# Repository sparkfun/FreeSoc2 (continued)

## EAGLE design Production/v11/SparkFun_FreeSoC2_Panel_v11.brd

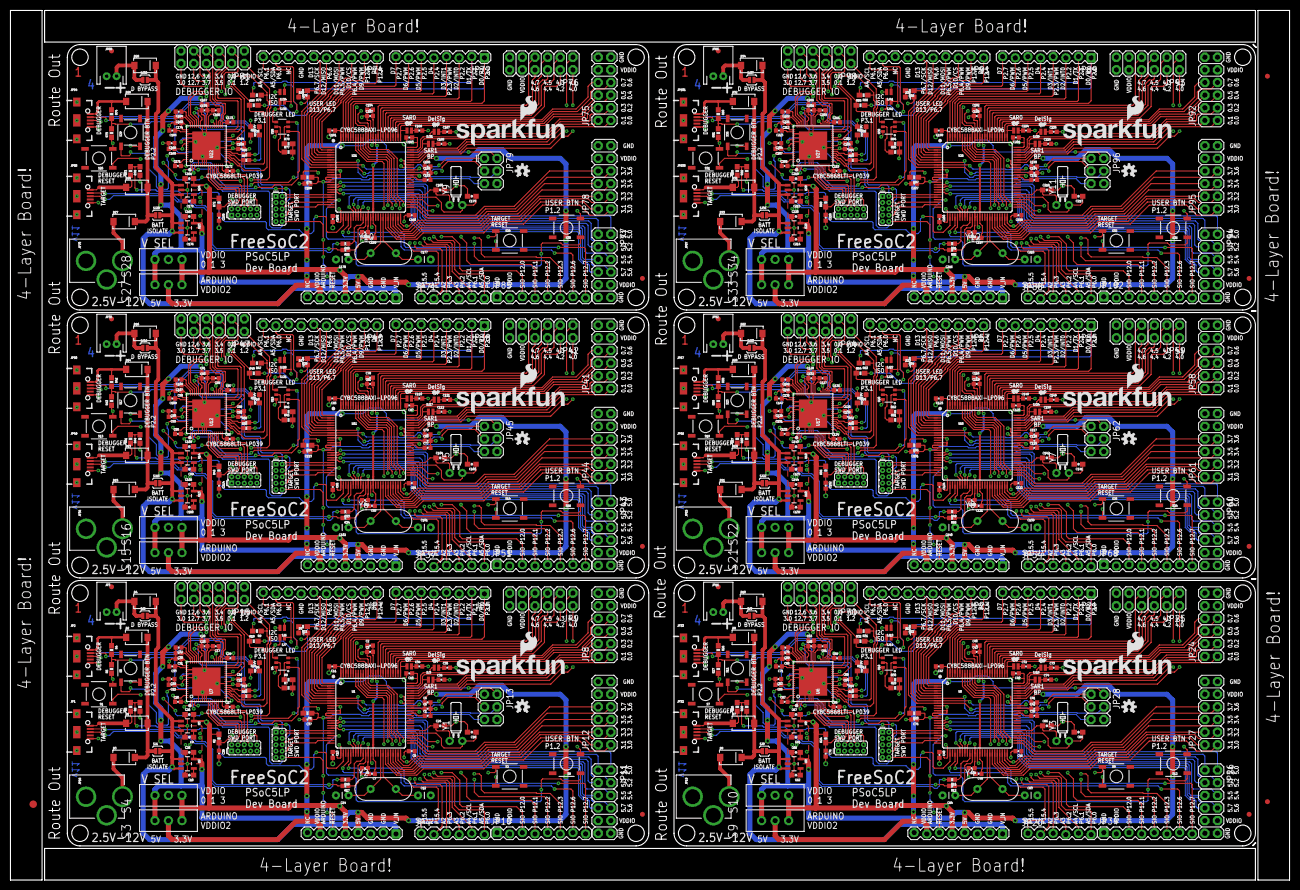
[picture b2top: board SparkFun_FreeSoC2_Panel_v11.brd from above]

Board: 4 copper layers, 257.0 x 174.8 mm, 633 parts (0 on the bottom side), 756 nets.

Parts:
C1, C2, C4, C5, C7, C16, C17, C19, C20, C39, C40, C41, C44, C45, C50, C51, C52, C53, C77, C78, C79, C82, C83, C88, C89, C90, C91, C115, C116, C117, C120, C121, C126, C127, C128, C129, C153, C154, C155, C158, C159, C164, C165, C166, C167, C191, C192, C193, C196, C197, C202, C203, C204, C205: 1.0uF; 0402-CAP
C3, C6, C9, C11, C13, C15, C21, C22, C23, C25, C27, C29, C30, C31, C32, C33, C34, C35, C36, C37, C38, C42, C43, C46, C47, C48, C49, C54, C55, C56, C57, C58, C59, C60, C69, C70, C71, C72, C73, C74, C75, C76, C80, C81, C84, C85, C86, C87, C92, C93, C94, C95, C96, C97, C98, C107, C108, C109, C110, C111, C112, C113, C114, C118, C119, C122, C123, C124, C125, C130, C131, C132, C133, C134, C135, C136, C145, C146, C147, C148, C149, C150, C151, C152, C156, C157, C160, C161, C162, C163, C168, C169, C170, C171, C172, C173, C174, C183, C184, C185, C186, C187, C188, C189, C190, C194, C195, C198, C199, C200, C201, C206, C207, C208, C209, C210, C211, C212, C221, C222, C223, C224, C225, C226, C227, C228: 0.1uF; 0402-CAP
C8, C10, C61, C62, C99, C100, C137, C138, C175, C176, C213, C214: 470pF; 0603-CAP
C12, C14, C63, C64, C101, C102, C139, C140, C177, C178, C215, C216: CAP-PTH-SMALL
C18, C24, C65, C66, C103, C104, C141, C142, C179, C180, C217, C218: 22pF; 0603-CAP
C26, C28, C67, C68, C105, C106, C143, C144, C181, C182, C219, C220: 2.2uF; 0603-CAP
D1, D2, D3, D4, D7, D8, D9, D10, D13, D14, D15, D16, D19, D20, D21, D22, D25, D26, D27, D28, D31, D32, D33, D34: MBRA140; SMA-DIODE
D5, D6, D11, D12, D17, D18, D23, D24, D29, D30, D35, D36: RED; LED-0603
E$1: FIDUCIAL-1.5X3
E$5, E$6: FIDUCIAL-1X2
FID1, FID2, FID3, FID4, FID5, FID6, FID7, FID8, FID9, FID10, FID11, FID12: FIDUCIAL1X2; FIDUCIAL-1X2
JP1, JP2, JP32, JP33, JP49, JP50, JP66, JP67, JP83, JP84, JP100, JP101: MicroB; USB-B-MICRO-SMD_V03
JP3, JP16, JP35, JP52, JP69, JP86: M02JST-PTH-2; JST-2-PTH
JP4, JP20, JP37, JP54, JP71, JP88: 1X6 FEMALE PTH; 1X06-SIP_LOCK
JP5, JP6, JP21, JP22, JP38, JP39, JP55, JP56, JP72, JP73, JP89, JP90: 1X8 FEMALE PTH; 1X08_LOCK
JP7, JP23, JP40, JP57, JP74, JP91: 1X10 FEMALE PTH; 1X10_LOCK
JP8, JP9, JP11, JP12, JP15, JP24, JP25, JP26, JP27, JP30, JP41, JP42, JP43, JP44, JP47, JP58, JP59, JP60, JP61, JP64, JP75, JP76, JP77, JP78, JP81, JP92, JP93, JP94, JP95, JP98: 2X6 FEMALE; 2X6
JP10, JP34, JP51, JP68, JP85, JP102: 1x8 FEMALE PTH; 1X08_LOCK
JP13, JP28, JP45, JP62, JP79, JP96: 2X3
JP14, JP17, JP29, JP31, JP46, JP48, JP63, JP65, JP80, JP82, JP97, JP99: DNP; 2X5_PTH_SILK_.05
JP18, JP19, JP36, JP53, JP70, JP87: POWER_JACKPTH_LOCK; POWER_JACK_PTH_LOCK
LOGO1, LOGO3, LOGO5, LOGO7, LOGO9, LOGO11: SFE_LOGO_NAME_FLAME.2_INCH; SFE_LOGO_NAME_FLAME_.2
LOGO2, LOGO4, LOGO6, LOGO8, LOGO10, LOGO12: OSHW-LOGOS; OSHW-LOGO-S
R1, R2, R23, R24, R39, R40, R55, R56, R71, R72, R87, R88: 4.7K; 0603-RES
R3, R4, R25, R26, R41, R42, R57, R58, R73, R74, R89, R90: 10K; 0603-RES
R5, R6, R27, R28, R43, R44, R59, R60, R75, R76, R91, R92: 20k; 0603-RES
R7, R8, R29, R30, R45, R46, R61, R62, R77, R78, R93, R94: 2.2k; 0603-RES
R9, R10, R15, R20, R21, R22, R31, R32, R37, R38, R47, R48, R53, R54, R63, R64, R69, R70, R79, R80, R85, R86, R95, R96: 1K; 0603-RES
R11, R12, R13, R14, R16, R17, R18, R19, R33, R34, R35, R36, R49, R50, R51, R52, R65, R66, R67, R68, R81, R82, R83, R84: 22; 0402-RES
S1, S2, S5, S6, S7, S8, S11, S12, S13, S14, S17, S18, S19, S20, S23, S24, S25, S26, S29, S30, S31, S32, S35, S36: SPST-MOM; TACTILE-SWITCH-SMD
S3, S4, S9, S10, S15, S16, S21, S22, S27, S28, S33, S34: SPDT; SWITCH-SPDT_LOCK.007S
SJ1, SJ8, SJ15, SJ22, SJ29, SJ36: JUMPER-PAD-2-NC_BY_PASTE; PAD-JUMPER-2-NC_BY_PASTE_YES_SILK
SJ2, SJ9, SJ16, SJ23, SJ30, SJ37: JUMPER-PAD-2-NOYES_SILK; PAD-JUMPER-2-NO_YES_SILK
SJ3, SJ4, SJ5, SJ6, SJ7, SJ10, SJ11, SJ12, SJ13, SJ14, SJ17, SJ18, SJ19, SJ20, SJ21, SJ24, SJ25, SJ26, SJ27, SJ28, SJ31, SJ32, SJ33, SJ34, SJ35, SJ38, SJ39, SJ40, SJ41, SJ42: JUMPER-PAD-2-NO; PAD-JUMPER-2-NO_NO_SILK
STANDOFF1, STANDOFF2, STANDOFF3, STANDOFF4, STANDOFF5, STANDOFF6, STANDOFF7, STANDOFF8, STANDOFF9, STANDOFF10, STANDOFF11, STANDOFF12, STANDOFF13, STANDOFF14, STANDOFF15, STANDOFF16, STANDOFF17, STANDOFF18, STANDOFF19, STANDOFF20, STANDOFF21, STANDOFF22, STANDOFF23, STANDOFF24: STAND-OFF
U1, U5, U11, U16, U21, U26: CY8C5888AXI-LP096; TQFP-100-14X14MM
U2, U8, U13, U18, U23, U28: MIC5219 5V; SOT23-5
U3, U9, U14, U19, U24, U29: MIC5219 3.3V; SOT23-5
U4, U10, U15, U20, U25, U30: 2A/20V; SOT26
U6, U7, U12, U17, U22, U27: CY8C5868LTI-LP039; QFN-68
Y1, Y3, Y5, Y7, Y9, Y11: 32.768kHz; TC26H
Y2, Y4, Y6, Y8, Y10, Y12: HC49US

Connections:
3.3V: C2.1, C3.1, C4.1, C19.1, C21.1, C22.1, C26.2, JP6.5, R1.2, R2.2, S3.3, S4.3, U1.37, U1.88, U3.5, U7.24, U7.59
3.3V1: C40.1, C43.1, C44.1, C52.1, C54.1, C55.1, C67.2, JP22.5, R23.2, R24.2, S9.3, S10.3, U5.37, U5.88, U6.24, U6.59, U9.5
3.3V2: C78.1, C81.1, C82.1, C90.1, C92.1, C93.1, C105.2, JP39.5, R39.2, R40.2, S15.3, S16.3, U11.37, U11.88, U12.24, U12.59, U14.5
3.3V3: C116.1, C119.1, C120.1, C128.1, C130.1, C131.1, C143.2, JP56.5, R55.2, R56.2, S21.3, S22.3, U16.37, U16.88, U17.24, U17.59, U19.5
3.3V4: C154.1, C157.1, C158.1, C166.1, C168.1, C169.1, C181.2, JP73.5, R71.2, R72.2, S27.3, S28.3, U21.37, U21.88, U22.24, U22.59, U24.5
3.3V5: C192.1, C195.1, C196.1, C204.1, C206.1, C207.1, C219.2, JP90.5, R87.2, R88.2, S33.3, S34.3, U26.37, U26.88, U27.24, U27.59, U29.5
5V: C5.1, C6.1, C20.1, C23.1, C28.2, JP6.4, S3.1, S4.1, U1.65, U2.5, U7.44
5V1: C41.1, C42.1, C53.1, C56.1, C68.2, JP22.4, S9.1, S10.1, U5.65, U6.44, U8.5
5V2: C79.1, C80.1, C91.1, C94.1, C106.2, JP39.4, S15.1, S16.1, U11.65, U12.44, U13.5
5V3: C117.1, C118.1, C129.1, C132.1, C144.2, JP56.4, S21.1, S22.1, U16.65, U17.44, U18.5
5V4: C155.1, C156.1, C167.1, C170.1, C182.2, JP73.4, S27.1, S28.1, U21.65, U22.44, U23.5
5V5: C193.1, C194.1, C205.1, C208.1, C220.2, JP90.4, S33.1, S34.1, U26.65, U27.44, U28.5
!DEBUG_P2.6_SCL_PU_EN: U4.G2, U7.1
!DEBUG_P2.6_SCL_PU_EN1: U6.1, U10.G2
!DEBUG_P2.6_SCL_PU_EN2: U12.1, U15.G2
!DEBUG_P2.6_SCL_PU_EN3: U17.1, U20.G2
!DEBUG_P2.6_SCL_PU_EN4: U22.1, U25.G2
!DEBUG_P2.6_SCL_PU_EN5: U27.1, U30.G2
!DEBUG_P2.7_SDA_PU_EN: U4.G1, U7.2
!DEBUG_P2.7_SDA_PU_EN1: U6.2, U10.G1
!DEBUG_P2.7_SDA_PU_EN2: U12.2, U15.G1
!DEBUG_P2.7_SDA_PU_EN3: U17.2, U20.G1
!DEBUG_P2.7_SDA_PU_EN4: U22.2, U25.G1
!DEBUG_P2.7_SDA_PU_EN5: U27.2, U30.G1
!DEBUG_RESET: C38.1, JP14.10, R2.1, S1.1, U7.10
!DEBUG_RESET1: C76.1, JP29.10, R24.1, S7.1, U6.10
!DEBUG_RESET2: C114.1, JP46.10, R40.1, S13.1, U12.10
!DEBUG_RESET3: C152.1, JP63.10, R56.1, S19.1, U17.10
!DEBUG_RESET4: C190.1, JP80.10, R72.1, S25.1, U22.10
!DEBUG_RESET5: C228.1, JP97.10, R88.1, S31.1, U27.10
!RESET: C37.1, JP6.6, JP13.5, JP17.10, R1.1, S2.1, U1.15, U7.3
!RESET1: C75.1, JP22.6, JP28.5, JP31.10, R23.1, S8.1, U5.15, U6.3
!RESET2: C113.1, JP39.6, JP45.5, JP48.10, R39.1, S14.1, U11.15, U12.3
!RESET3: C151.1, JP56.6, JP62.5, JP65.10, R55.1, S20.1, U16.15, U17.3
!RESET4: C189.1, JP73.6, JP79.5, JP82.10, R71.1, S26.1, U21.15, U22.3
!RESET5: C227.1, JP90.6, JP96.5, JP99.10, R87.1, S32.1, U26.15, U27.3
A0: JP4.1, U1.94
A1: JP4.2, U1.93
A2: JP4.3, U1.92
A3: JP4.4, U1.91
A4: JP4.5, JP7.10, SJ7.1, U1.90
A5: JP4.6, JP7.9, SJ6.1, U1.89
A6: JP20.1, U5.94
A7: JP20.2, U5.93
A8: JP20.6, JP23.9, SJ13.1, U5.89
A9: JP20.5, JP23.10, SJ14.1, U5.90
A10: JP20.3, U5.92
A11: JP20.4, U5.91
A12: JP37.1, U11.94
A13: JP37.2, U11.93
A14: JP37.6, JP40.9, SJ20.1, U11.89
A15: JP37.5, JP40.10, SJ21.1, U11.90
A16: JP37.3, U11.92
A17: JP37.4, U11.91
A18: JP54.1, U16.94
A19: JP54.2, U16.93
A20: JP54.6, JP57.9, SJ27.1, U16.89
A21: JP54.5, JP57.10, SJ28.1, U16.90
A22: JP54.3, U16.92
A23: JP54.4, U16.91
A24: JP71.1, U21.94
A25: JP71.2, U21.93
A26: JP71.6, JP74.9, SJ34.1, U21.89
A27: JP71.5, JP74.10, SJ35.1, U21.90
A28: JP71.3, U21.92
A29: JP71.4, U21.91
A30: JP88.1, U26.94
A31: JP88.2, U26.93
A32: JP88.6, JP91.9, SJ41.1, U26.89
A33: JP88.5, JP91.10, SJ42.1, U26.90
A34: JP88.3, U26.92
A35: JP88.4, U26.91
D0: JP5.1, R10.2, U1.95
D1: JP5.2, R9.2, U1.96
D2: JP5.3, U1.97
D3: JP5.4, U1.98
D4: JP5.5, U1.99
D5: JP5.6, U1.1
D6: JP5.7, U1.2
D7: JP5.8, U1.3
D8: JP7.1, U1.4
D9: JP7.2, U1.5
D10: JP7.3, U1.6
D11: JP7.4, JP13.4, U1.7
D12: JP7.5, JP13.1, U1.8
D13: JP7.6, JP13.3, R21.1, U1.9
D14: JP21.1, R32.2, U5.95
D15: JP21.2, R31.2, U5.96
D16: JP21.3, U5.97
D17: JP21.4, U5.98
D18: JP21.5, U5.99
D19: JP21.6, U5.1
D20: JP21.7, U5.2
D21: JP21.8, U5.3
D22: JP23.1, U5.4
D23: JP23.2, U5.5
D24: JP23.3, U5.6
D25: JP23.4, JP28.4, U5.7
D26: JP23.5, JP28.1, U5.8
D27: JP23.6, JP28.3, R22.1, U5.9
D28: JP38.1, R48.2, U11.95
D29: JP38.2, R47.2, U11.96
D30: JP38.3, U11.97
D31: JP38.4, U11.98
D32: JP38.5, U11.99
D33: JP38.6, U11.1
D34: JP38.7, U11.2
D35: JP38.8, U11.3
D36: JP40.1, U11.4
D37: JP40.2, U11.5
D38: JP40.3, U11.6
D39: JP40.4, JP45.4, U11.7
D40: JP40.5, JP45.1, U11.8
D41: JP40.6, JP45.3, R38.1, U11.9
D42: JP55.1, R64.2, U16.95
D43: JP55.2, R63.2, U16.96
D44: JP55.3, U16.97
D45: JP55.4, U16.98
D46: JP55.5, U16.99
D47: JP55.6, U16.1
D48: JP55.7, U16.2
D49: JP55.8, U16.3
D50: JP57.1, U16.4
D51: JP57.2, U16.5
D52: JP57.3, U16.6
D53: JP57.4, JP62.4, U16.7
D54: JP57.5, JP62.1, U16.8
D55: JP57.6, JP62.3, R54.1, U16.9
D56: JP72.1, R80.2, U21.95
D57: JP72.2, R79.2, U21.96
D58: JP72.3, U21.97
D59: JP72.4, U21.98
D60: JP72.5, U21.99
D61: JP72.6, U21.1
D62: JP72.7, U21.2
D63: JP72.8, U21.3
D64: JP74.1, U21.4
D65: JP74.2, U21.5
D66: JP74.3, U21.6
D67: JP74.4, JP79.4, U21.7
D68: JP74.5, JP79.1, U21.8
D69: JP74.6, JP79.3, R70.1, U21.9
D70: JP89.1, R96.2, U26.95
D71: JP89.2, R95.2, U26.96
D72: JP89.3, U26.97
D73: JP89.4, U26.98
D74: JP89.5, U26.99
D75: JP89.6, U26.1
D76: JP89.7, U26.2
D77: JP89.8, U26.3
D78: JP91.1, U26.4
D79: JP91.2, U26.5
D80: JP91.3, U26.6
D81: JP91.4, JP96.4, U26.7
D82: JP91.5, JP96.1, U26.8
D83: JP91.6, JP96.3, R86.1, U26.9
DEBUG_BTN: S5.1, U7.64
DEBUG_BTN1: S11.1, U6.64
DEBUG_BTN2: S17.1, U12.64
DEBUG_BTN3: S23.1, U17.64
DEBUG_BTN4: S29.1, U22.64
DEBUG_BTN5: S35.1, U27.64
DEBUG_D+_BUS: JP2.D+1, R18.2
DEBUG_D+_BUS1: JP33.D+1, R13.2
DEBUG_D+_BUS2: JP50.D+1, R35.2
DEBUG_D+_BUS3: JP67.D+1, R51.2
DEBUG_D+_BUS4: JP84.D+1, R67.2
DEBUG_D+_BUS5: JP101.D+1, R83.2
DEBUG_D+_PAD: R18.1, U7.22
DEBUG_D+_PAD1: R13.1, U6.22
DEBUG_D+_PAD2: R35.1, U12.22
DEBUG_D+_PAD3: R51.1, U17.22
DEBUG_D+_PAD4: R67.1, U22.22
DEBUG_D+_PAD5: R83.1, U27.22
DEBUG_D-_BUS: JP2.D-1, R19.2
DEBUG_D-_BUS1: JP33.D-1, R14.2
DEBUG_D-_BUS2: JP50.D-1, R36.2
DEBUG_D-_BUS3: JP67.D-1, R52.2
DEBUG_D-_BUS4: JP84.D-1, R68.2
DEBUG_D-_BUS5: JP101.D-1, R84.2
DEBUG_D-_PAD: R19.1, U7.23
DEBUG_D-_PAD1: R14.1, U6.23
DEBUG_D-_PAD2: R36.1, U12.23
DEBUG_D-_PAD3: R52.1, U17.23
DEBUG_D-_PAD4: R68.1, U22.23
DEBUG_D-_PAD5: R84.1, U27.23
DEBUG_DS_BP: C30.1, U7.51
DEBUG_DS_BP1: C69.1, U6.51
DEBUG_DS_BP2: C107.1, U12.51
DEBUG_DS_BP3: C145.1, U17.51
DEBUG_DS_BP4: C183.1, U22.51
DEBUG_DS_BP5: C221.1, U27.51
DEBUG_LED: R20.1, U7.30
DEBUG_LED1: R15.1, U6.30
DEBUG_LED2: R37.1, U12.30
DEBUG_LED3: R53.1, U17.30
DEBUG_LED4: R69.1, U22.30
DEBUG_LED5: R85.1, U27.30
DEBUG_P0.0: JP15.3, U7.48
DEBUG_P0.1: JP15.4, U7.49
DEBUG_P0.2: JP30.3, U6.48
DEBUG_P0.3: JP30.4, U6.49
DEBUG_P0.4: JP47.3, U12.48
DEBUG_P0.5: JP47.4, U12.49
DEBUG_P0.6: JP64.3, U17.48
DEBUG_P0.7: JP64.4, U17.49
DEBUG_P0.8: JP81.3, U22.48
DEBUG_P0.9: JP81.4, U22.49
DEBUG_P0.10: JP98.3, U27.48
DEBUG_P0.11: JP98.4, U27.49
DEBUG_P1.1: JP30.2, U6.13
DEBUG_P1.2: JP15.2, U7.13
DEBUG_P1.3: JP47.2, U12.13
DEBUG_P1.4: JP64.2, U17.13
DEBUG_P1.5: JP81.2, U22.13
DEBUG_P1.6: JP98.2, U27.13
DEBUG_P3.0: JP15.12, U7.29
DEBUG_P3.1: JP30.5, U6.33
DEBUG_P3.2: JP30.6, U6.34
DEBUG_P3.3: JP30.7, U6.36
DEBUG_P3.4: JP15.5, U7.33
DEBUG_P3.5: JP15.6, U7.34
DEBUG_P3.6: JP15.7, U7.36
DEBUG_P3.7: JP15.8, U7.37
DEBUG_P3.8: JP30.8, U6.37
DEBUG_P3.9: JP30.12, U6.29
DEBUG_P3.10: JP47.5, U12.33
DEBUG_P3.11: JP47.6, U12.34
DEBUG_P3.12: JP47.7, U12.36
DEBUG_P3.13: JP47.8, U12.37
DEBUG_P3.14: JP47.12, U12.29
DEBUG_P3.15: JP64.5, U17.33
DEBUG_P3.16: JP64.6, U17.34
DEBUG_P3.17: JP64.7, U17.36
DEBUG_P3.18: JP64.8, U17.37
DEBUG_P3.19: JP64.12, U17.29
DEBUG_P3.20: JP81.5, U22.33
DEBUG_P3.21: JP81.6, U22.34
DEBUG_P3.22: JP81.7, U22.36
DEBUG_P3.23: JP81.8, U22.37
DEBUG_P3.24: JP81.12, U22.29
DEBUG_P3.25: JP98.5, U27.33
DEBUG_P3.26: JP98.6, U27.34
DEBUG_P3.27: JP98.7, U27.36
DEBUG_P3.28: JP98.8, U27.37
DEBUG_P3.29: JP98.12, U27.29
DEBUG_P12.0_SCL: SJ7.2, U4.D2, U7.39
DEBUG_P12.0_SCL1: SJ14.2, U6.39, U10.D2
DEBUG_P12.0_SCL2: SJ21.2, U12.39, U15.D2
DEBUG_P12.0_SCL3: SJ28.2, U17.39, U20.D2
DEBUG_P12.0_SCL4: SJ35.2, U22.39, U25.D2
DEBUG_P12.0_SCL5: SJ42.2, U27.39, U30.D2
DEBUG_P12.1_SDA: SJ6.2, U4.D1, U7.38
DEBUG_P12.1_SDA1: SJ13.2, U6.38, U10.D1
DEBUG_P12.1_SDA2: SJ20.2, U12.38, U15.D1
DEBUG_P12.1_SDA3: SJ27.2, U17.38, U20.D1
DEBUG_P12.1_SDA4: SJ34.2, U22.38, U25.D1
DEBUG_P12.1_SDA5: SJ41.2, U27.38, U30.D1
DEBUG_P12.6_RX: JP15.9, R9.1, U7.20
DEBUG_P12.6_RX1: JP30.9, R31.1, U6.20
DEBUG_P12.6_RX2: JP47.9, R47.1, U12.20
DEBUG_P12.6_RX3: JP64.9, R63.1, U17.20
DEBUG_P12.6_RX4: JP81.9, R79.1, U22.20
DEBUG_P12.6_RX5: JP98.9, R95.1, U27.20
DEBUG_P12.7_TX: JP15.10, R10.1, U7.21
DEBUG_P12.7_TX1: JP30.10, R32.1, U6.21
DEBUG_P12.7_TX2: JP47.10, R48.1, U12.21
DEBUG_P12.7_TX3: JP64.10, R64.1, U17.21
DEBUG_P12.7_TX4: JP81.10, R80.1, U22.21
DEBUG_P12.7_TX5: JP98.10, R96.1, U27.21
DEBUG_SAR0_BP: C33.1, U7.53
DEBUG_SAR0_BP1: C71.1, U6.53
DEBUG_SAR0_BP2: C109.1, U12.53
DEBUG_SAR0_BP3: C147.1, U17.53
DEBUG_SAR0_BP4: C185.1, U22.53
DEBUG_SAR0_BP5: C223.1, U27.53
DEBUG_SAR1_BP: C32.1, U7.50
DEBUG_SAR1_BP1: C70.1, U6.50
DEBUG_SAR1_BP2: C108.1, U12.50
DEBUG_SAR1_BP3: C146.1, U17.50
DEBUG_SAR1_BP4: C184.1, U22.50
DEBUG_SAR1_BP5: C222.1, U27.50
DEBUG_SWDCK_TCK: JP14.4, U7.12
DEBUG_SWDCK_TCK1: JP29.4, U6.12
DEBUG_SWDCK_TCK2: JP46.4, U12.12
DEBUG_SWDCK_TCK3: JP63.4, U17.12
DEBUG_SWDCK_TCK4: JP80.4, U22.12
DEBUG_SWDCK_TCK5: JP97.4, U27.12
DEBUG_SWDIO_TMS: JP14.2, U7.11
DEBUG_SWDIO_TMS1: JP29.2, U6.11
DEBUG_SWDIO_TMS2: JP46.2, U12.11
DEBUG_SWDIO_TMS3: JP63.2, U17.11
DEBUG_SWDIO_TMS4: JP80.2, U22.11
DEBUG_SWDIO_TMS5: JP97.2, U27.11
DEBUG_SWV_TDO: JP14.6, U7.14
DEBUG_SWV_TDO1: JP29.6, U6.14
DEBUG_SWV_TDO2: JP46.6, U12.14
DEBUG_SWV_TDO3: JP63.6, U17.14
DEBUG_SWV_TDO4: JP80.6, U22.14
DEBUG_SWV_TDO5: JP97.6, U27.14
DEBUG_TDI: JP14.8, U7.15
DEBUG_TDI1: JP29.8, U6.15
DEBUG_TDI2: JP46.8, U12.15
DEBUG_TDI3: JP63.8, U17.15
DEBUG_TDI4: JP80.8, U22.15
DEBUG_TDI5: JP97.8, U27.15
GND: C1.2, C2.2, C3.2, C4.2, C5.2, C6.2, C7.2, C8.2, C9.2, C10.2, C11.2, C12.2, C13.2, C14.2, C15.2, C16.2, C17.2, C18.2, C19.2, C20.2, C21.2, C22.2, C23.2, C24.2, C25.2, C26.1, C27.2, C28.1, C29.2, C30.2, C31.2, C32.2, C33.2, C34.2, C35.2, C36.2, C37.2, C38.2, D5.C, D6.C, JP1.GND1, JP1.SHIELD1, JP1.SHIELD2, JP1.SHIELD3, JP2.GND1, JP2.SHIELD1, JP2.SHIELD2, JP2.SHIELD3, JP3.1, JP6.2, JP6.3, JP7.7, JP8.11, JP8.12, JP9.11, JP9.12, JP10.1, JP11.11, JP11.12, JP12.11, JP12.12, JP13.6, JP14.3, JP14.5, JP14.7, JP14.9, JP15.11, JP17.3, JP17.5, JP17.7, JP17.9, JP18.GND, JP18.GNDBREAK, R5.1, R6.1, S1.3, S2.3, S5.3, S6.3, U1.10, U1.12, U1.13, U1.14, U1.38, U1.64, U1.66, U1.87, U2.2, U3.2, U7.5, U7.7, U7.8, U7.9, U7.25, U7.43, U7.45, U7.54, U7.56, U7.58, U7.69
GND1: C39.2, C40.2, C41.2, C42.2, C43.2, C44.2, C45.2, C46.2, C47.2, C48.2, C49.2, C50.2, C51.2, C52.2, C53.2, C54.2, C55.2, C56.2, C57.2, C58.2, C59.2, C60.2, C61.2, C62.2, C63.2, C64.2, C65.2, C66.2, C67.1, C68.1, C69.2, C70.2, C71.2, C72.2, C73.2, C74.2, C75.2, C76.2, D11.C, D12.C, JP16.1, JP19.GND, JP19.GNDBREAK, JP22.2, JP22.3, JP23.7, JP24.11, JP24.12, JP25.11, JP25.12, JP26.11, JP26.12, JP27.11, JP27.12, JP28.6, JP29.3, JP29.5, JP29.7, JP29.9, JP30.11, JP31.3, JP31.5, JP31.7, JP31.9, JP32.GND1, JP32.SHIELD1, JP32.SHIELD2, JP32.SHIELD3, JP33.GND1, JP33.SHIELD1, JP33.SHIELD2, JP33.SHIELD3, JP34.1, R27.1, R28.1, S7.3, S8.3, S11.3, S12.3, U5.10, U5.12, U5.13, U5.14, U5.38, U5.64, U5.66, U5.87, U6.5, U6.7, U6.8, U6.9, U6.25, U6.43, U6.45, U6.54, U6.56, U6.58, U6.69, U8.2, U9.2
GND2: C77.2, C78.2, C79.2, C80.2, C81.2, C82.2, C83.2, C84.2, C85.2, C86.2, C87.2, C88.2, C89.2, C90.2, C91.2, C92.2, C93.2, C94.2, C95.2, C96.2, C97.2, C98.2, C99.2, C100.2, C101.2, C102.2, C103.2, C104.2, C105.1, C106.1, C107.2, C108.2, C109.2, C110.2, C111.2, C112.2, C113.2, C114.2, D17.C, D18.C, JP35.1, JP36.GND, JP36.GNDBREAK, JP39.2, JP39.3, JP40.7, JP41.11, JP41.12, JP42.11, JP42.12, JP43.11, JP43.12, JP44.11, JP44.12, JP45.6, JP46.3, JP46.5, JP46.7, JP46.9, JP47.11, JP48.3, JP48.5, JP48.7, JP48.9, JP49.GND1, JP49.SHIELD1, JP49.SHIELD2, JP49.SHIELD3, JP50.GND1, JP50.SHIELD1, JP50.SHIELD2, JP50.SHIELD3, JP51.1, R43.1, R44.1, S13.3, S14.3, S17.3, S18.3, U11.10, U11.12, U11.13, U11.14, U11.38, U11.64, U11.66, U11.87, U12.5, U12.7, U12.8, U12.9, U12.25, U12.43, U12.45, U12.54, U12.56, U12.58, U12.69, U13.2, U14.2
GND3: C115.2, C116.2, C117.2, C118.2, C119.2, C120.2, C121.2, C122.2, C123.2, C124.2, C125.2, C126.2, C127.2, C128.2, C129.2, C130.2, C131.2, C132.2, C133.2, C134.2, C135.2, C136.2, C137.2, C138.2, C139.2, C140.2, C141.2, C142.2, C143.1, C144.1, C145.2, C146.2, C147.2, C148.2, C149.2, C150.2, C151.2, C152.2, D23.C, D24.C, JP52.1, JP53.GND, JP53.GNDBREAK, JP56.2, JP56.3, JP57.7, JP58.11, JP58.12, JP59.11, JP59.12, JP60.11, JP60.12, JP61.11, JP61.12, JP62.6, JP63.3, JP63.5, JP63.7, JP63.9, JP64.11, JP65.3, JP65.5, JP65.7, JP65.9, JP66.GND1, JP66.SHIELD1, JP66.SHIELD2, JP66.SHIELD3, JP67.GND1, JP67.SHIELD1, JP67.SHIELD2, JP67.SHIELD3, JP68.1, R59.1, R60.1, S19.3, S20.3, S23.3, S24.3, U16.10, U16.12, U16.13, U16.14, U16.38, U16.64, U16.66, U16.87, U17.5, U17.7, U17.8, U17.9, U17.25, U17.43, U17.45, U17.54, U17.56, U17.58, U17.69, U18.2, U19.2
GND4: C153.2, C154.2, C155.2, C156.2, C157.2, C158.2, C159.2, C160.2, C161.2, C162.2, C163.2, C164.2, C165.2, C166.2, C167.2, C168.2, C169.2, C170.2, C171.2, C172.2, C173.2, C174.2, C175.2, C176.2, C177.2, C178.2, C179.2, C180.2, C181.1, C182.1, C183.2, C184.2, C185.2, C186.2, C187.2, C188.2, C189.2, C190.2, D29.C, D30.C, JP69.1, JP70.GND, JP70.GNDBREAK, JP73.2, JP73.3, JP74.7, JP75.11, JP75.12, JP76.11, JP76.12, JP77.11, JP77.12, JP78.11, JP78.12, JP79.6, JP80.3, JP80.5, JP80.7, JP80.9, JP81.11, JP82.3, JP82.5, JP82.7, JP82.9, JP83.GND1, JP83.SHIELD1, JP83.SHIELD2, JP83.SHIELD3, JP84.GND1, JP84.SHIELD1, JP84.SHIELD2, JP84.SHIELD3, JP85.1, R75.1, R76.1, S25.3, S26.3, S29.3, S30.3, U21.10, U21.12, U21.13, U21.14, U21.38, U21.64, U21.66, U21.87, U22.5, U22.7, U22.8, U22.9, U22.25, U22.43, U22.45, U22.54, U22.56, U22.58, U22.69, U23.2, U24.2
GND5: C191.2, C192.2, C193.2, C194.2, C195.2, C196.2, C197.2, C198.2, C199.2, C200.2, C201.2, C202.2, C203.2, C204.2, C205.2, C206.2, C207.2, C208.2, C209.2, C210.2, C211.2, C212.2, C213.2, C214.2, C215.2, C216.2, C217.2, C218.2, C219.1, C220.1, C221.2, C222.2, C223.2, C224.2, C225.2, C226.2, C227.2, C228.2, D35.C, D36.C, JP86.1, JP87.GND, JP87.GNDBREAK, JP90.2, JP90.3, JP91.7, JP92.11, JP92.12, JP93.11, JP93.12, JP94.11, JP94.12, JP95.11, JP95.12, JP96.6, JP97.3, JP97.5, JP97.7, JP97.9, JP98.11, JP99.3, JP99.5, JP99.7, JP99.9, JP100.GND1, JP100.SHIELD1, JP100.SHIELD2, JP100.SHIELD3, JP101.GND1, JP101.SHIELD1, JP101.SHIELD2, JP101.SHIELD3, JP102.1, R91.1, R92.1, S31.3, S32.3, S35.3, S36.3, U26.10, U26.12, U26.13, U26.14, U26.38, U26.64, U26.66, U26.87, U27.5, U27.7, U27.8, U27.9, U27.25, U27.43, U27.45, U27.54, U27.56, U27.58, U27.69, U28.2, U29.2
unnamed: C8.1, U3.4
unnamed: C10.1, U2.4
unnamed: C34.1, SJ5.2
unnamed: C35.1, SJ4.2
unnamed: C36.1, SJ3.2
unnamed: D9.A, JP19.PWR
unnamed: R8.1, U4.S2
unnamed: R7.1, U4.S1
unnamed: D7.C, D8.C, D9.C, SJ8.1
unnamed: D10.A, JP16.2, SJ9.1
unnamed: C50.1, U6.26, U6.57
unnamed: D12.A, R15.2
unnamed: D3.A, JP18.PWR
unnamed: C16.1, U7.26, U7.57
unnamed: D11.A, R22.2
unnamed: D1.C, D2.C, D3.C, SJ1.1
unnamed: D4.A, JP3.2, SJ2.1
unnamed: C51.1, U6.42
unnamed: C61.1, U9.4
unnamed: C62.1, U8.4
unnamed: C72.1, SJ12.2
unnamed: C73.1, SJ11.2
unnamed: D6.A, R20.2
unnamed: C74.1, SJ10.2
unnamed: R30.1, U10.S2
unnamed: D5.A, R21.2
unnamed: C17.1, U7.42
unnamed: R29.1, U10.S1
unnamed: D15.A, JP36.PWR
unnamed: D13.C, D14.C, D15.C, SJ15.1
unnamed: D16.A, JP35.2, SJ16.1
unnamed: C88.1, U12.26, U12.57
unnamed: D18.A, R37.2
unnamed: D17.A, R38.2
unnamed: C89.1, U12.42
unnamed: C99.1, U14.4
unnamed: C100.1, U13.4
unnamed: C110.1, SJ19.2
unnamed: C111.1, SJ18.2
unnamed: C112.1, SJ17.2
unnamed: R46.1, U15.S2
unnamed: R45.1, U15.S1
unnamed: D21.A, JP53.PWR
unnamed: D19.C, D20.C, D21.C, SJ22.1
unnamed: D22.A, JP52.2, SJ23.1
unnamed: C126.1, U17.26, U17.57
unnamed: D24.A, R53.2
unnamed: D23.A, R54.2
unnamed: C127.1, U17.42
unnamed: C137.1, U19.4
unnamed: C138.1, U18.4
unnamed: C148.1, SJ26.2
unnamed: C149.1, SJ25.2
unnamed: C150.1, SJ24.2
unnamed: R62.1, U20.S2
unnamed: R61.1, U20.S1
unnamed: D27.A, JP70.PWR
unnamed: D25.C, D26.C, D27.C, SJ29.1
unnamed: D28.A, JP69.2, SJ30.1
unnamed: C164.1, U22.26, U22.57
unnamed: D30.A, R69.2
unnamed: D29.A, R70.2
unnamed: C165.1, U22.42
unnamed: C175.1, U24.4
unnamed: C176.1, U23.4
unnamed: C186.1, SJ33.2
unnamed: C187.1, SJ32.2
unnamed: C188.1, SJ31.2
unnamed: R78.1, U25.S2
unnamed: R77.1, U25.S1
unnamed: D33.A, JP87.PWR
unnamed: D31.C, D32.C, D33.C, SJ36.1
unnamed: D34.A, JP86.2, SJ37.1
unnamed: C202.1, U27.26, U27.57
unnamed: D36.A, R85.2
unnamed: D35.A, R86.2
unnamed: C203.1, U27.42
unnamed: C213.1, U29.4
unnamed: C214.1, U28.4
unnamed: C224.1, SJ40.2
unnamed: C225.1, SJ39.2
unnamed: C226.1, SJ38.2
unnamed: R94.1, U30.S2
unnamed: R93.1, U30.S1
P0.0: JP8.1, U1.71
P0.1: JP8.2, U1.72
P0.2: JP8.3, SJ3.1, U1.73
P0.3: JP8.4, SJ4.1, U1.74
P0.4: JP8.5, SJ5.1, U1.76
P0.5: JP8.6, U1.77
P0.6: JP8.7, U1.78
P0.7: JP8.8, U1.79
P0.8: JP24.1, U5.71
P0.9: JP24.2, U5.72
P0.10: JP24.3, SJ10.1, U5.73
P0.11: JP24.4, SJ11.1, U5.74
P0.12: JP24.5, SJ12.1, U5.76
P0.13: JP24.6, U5.77
P0.14: JP24.7, U5.78
P0.15: JP24.8, U5.79
P0.16: JP41.1, U11.71
P0.17: JP41.2, U11.72
P0.18: JP41.3, SJ17.1, U11.73
P0.19: JP41.4, SJ18.1, U11.74
P0.20: JP41.5, SJ19.1, U11.76
P0.21: JP41.6, U11.77
P0.22: JP41.7, U11.78
P0.23: JP41.8, U11.79
P0.24: JP58.1, U16.71
P0.25: JP58.2, U16.72
P0.26: JP58.3, SJ24.1, U16.73
P0.27: JP58.4, SJ25.1, U16.74
P0.28: JP58.5, SJ26.1, U16.76
P0.29: JP58.6, U16.77
P0.30: JP58.7, U16.78
P0.31: JP58.8, U16.79
P0.32: JP75.1, U21.71
P0.33: JP75.2, U21.72
P0.34: JP75.3, SJ31.1, U21.73
P0.35: JP75.4, SJ32.1, U21.74
P0.36: JP75.5, SJ33.1, U21.76
P0.37: JP75.6, U21.77
P0.38: JP75.7, U21.78
P0.39: JP75.8, U21.79
P0.40: JP92.1, U26.71
P0.41: JP92.2, U26.72
P0.42: JP92.3, SJ38.1, U26.73
P0.43: JP92.4, SJ39.1, U26.74
P0.44: JP92.5, SJ40.1, U26.76
P0.45: JP92.6, U26.77
P0.46: JP92.7, U26.78
P0.47: JP92.8, U26.79
P1.0: JP17.2, U1.20, U7.46
P1.1: JP17.4, U1.21, U7.47
P1.2: S6.1, U1.22
P1.3: JP17.6, U1.23
P1.4: JP17.8, U1.24
P1.5: JP31.2, U5.20, U6.46
P1.6: JP31.4, U5.21, U6.47
P1.7: S12.1, U5.22
P1.8: JP31.6, U5.23
P1.9: JP31.8, U5.24
P1.10: JP48.2, U11.20, U12.46
P1.11: JP48.4, U11.21, U12.47
P1.12: S18.1, U11.22
P1.13: JP48.6, U11.23
P1.14: JP48.8, U11.24
P1.15: JP65.2, U16.20, U17.46
P1.16: JP65.4, U16.21, U17.47
P1.17: S24.1, U16.22
P1.18: JP65.6, U16.23
P1.19: JP65.8, U16.24
P1.20: JP82.2, U21.20, U22.46
P1.21: JP82.4, U21.21, U22.47
P1.22: S30.1, U21.22
P1.23: JP82.6, U21.23
P1.24: JP82.8, U21.24
P1.25: JP99.2, U26.20, U27.46
P1.26: JP99.4, U26.21, U27.47
P1.27: S36.1, U26.22
P1.28: JP99.6, U26.23
P1.29: JP99.8, U26.24
P3.0: JP12.1, U1.44
P3.1: JP12.2, U1.45
P3.2: JP12.3, U1.46
P3.3: JP12.4, U1.47
P3.4: JP12.5, U1.48
P3.5: JP12.6, U1.49
P3.6: JP12.7, U1.51
P3.7: JP12.8, U1.52
P3.8: JP27.1, U5.44
P3.9: JP27.2, U5.45
P3.10: JP27.3, U5.46
P3.11: JP27.4, U5.47
P3.12: JP27.5, U5.48
P3.13: JP27.6, U5.49
P3.14: JP27.7, U5.51
P3.15: JP27.8, U5.52
P3.16: JP44.1, U11.44
P3.17: JP44.2, U11.45
P3.18: JP44.3, U11.46
P3.19: JP44.4, U11.47
P3.20: JP44.5, U11.48
P3.21: JP44.6, U11.49
P3.22: JP44.7, U11.51
P3.23: JP44.8, U11.52
P3.24: JP61.1, U16.44
P3.25: JP61.2, U16.45
P3.26: JP61.3, U16.46
P3.27: JP61.4, U16.47
P3.28: JP61.5, U16.48
P3.29: JP61.6, U16.49
P3.30: JP61.7, U16.51
P3.31: JP61.8, U16.52
P3.32: JP78.1, U21.44
P3.33: JP78.2, U21.45
P3.34: JP78.3, U21.46
P3.35: JP78.4, U21.47
P3.36: JP78.5, U21.48
P3.37: JP78.6, U21.49
P3.38: JP78.7, U21.51
P3.39: JP78.8, U21.52
P3.40: JP95.1, U26.44
P3.41: JP95.2, U26.45
P3.42: JP95.3, U26.46
P3.43: JP95.4, U26.47
P3.44: JP95.5, U26.48
P3.45: JP95.6, U26.49
P3.46: JP95.7, U26.51
P3.47: JP95.8, U26.52
P4.0: JP9.2, U1.69
P4.1: JP9.1, U1.70
P4.2: JP9.4, U1.80
P4.3: JP9.3, U1.81
P4.4: JP9.6, U1.82
P4.5: JP9.5, U1.83
P4.6: JP9.8, U1.84
P4.7: JP9.7, U1.85
P4.8: JP25.2, U5.69
P4.9: JP25.1, U5.70
P4.10: JP25.4, U5.80
P4.11: JP25.3, U5.81
P4.12: JP25.6, U5.82
P4.13: JP25.5, U5.83
P4.14: JP25.8, U5.84
P4.15: JP25.7, U5.85
P4.16: JP42.2, U11.69
P4.17: JP42.1, U11.70
P4.18: JP42.4, U11.80
P4.19: JP42.3, U11.81
P4.20: JP42.6, U11.82
P4.21: JP42.5, U11.83
P4.22: JP42.8, U11.84
P4.23: JP42.7, U11.85
P4.24: JP59.2, U16.69
P4.25: JP59.1, U16.70
P4.26: JP59.4, U16.80
P4.27: JP59.3, U16.81
P4.28: JP59.6, U16.82
P4.29: JP59.5, U16.83
P4.30: JP59.8, U16.84
P4.31: JP59.7, U16.85
P4.32: JP76.2, U21.69
P4.33: JP76.1, U21.70
P4.34: JP76.4, U21.80
P4.35: JP76.3, U21.81
P4.36: JP76.6, U21.82
P4.37: JP76.5, U21.83
P4.38: JP76.8, U21.84
P4.39: JP76.7, U21.85
P4.40: JP93.2, U26.69
P4.41: JP93.1, U26.70
P4.42: JP93.4, U26.80
P4.43: JP93.3, U26.81
P4.44: JP93.6, U26.82
P4.45: JP93.5, U26.83
P4.46: JP93.8, U26.84
P4.47: JP93.7, U26.85
P5.0: JP11.2, U1.16
P5.1: JP11.1, U1.17
P5.2: JP11.4, U1.18
P5.3: JP11.3, U1.19
P5.4: JP11.6, U1.31
P5.5: JP11.5, U1.32
P5.6: JP11.8, U1.33
P5.7: JP11.7, U1.34
P5.8: JP26.2, U5.16
P5.9: JP26.1, U5.17
P5.10: JP26.4, U5.18
P5.11: JP26.3, U5.19
P5.12: JP26.6, U5.31
P5.13: JP26.5, U5.32
P5.14: JP26.8, U5.33
P5.15: JP26.7, U5.34
P5.16: JP43.2, U11.16
P5.17: JP43.1, U11.17
P5.18: JP43.4, U11.18
P5.19: JP43.3, U11.19
P5.20: JP43.6, U11.31
P5.21: JP43.5, U11.32
P5.22: JP43.8, U11.33
P5.23: JP43.7, U11.34
P5.24: JP60.2, U16.16
P5.25: JP60.1, U16.17
P5.26: JP60.4, U16.18
P5.27: JP60.3, U16.19
P5.28: JP60.6, U16.31
P5.29: JP60.5, U16.32
P5.30: JP60.8, U16.33
P5.31: JP60.7, U16.34
P5.32: JP77.2, U21.16
P5.33: JP77.1, U21.17
P5.34: JP77.4, U21.18
P5.35: JP77.3, U21.19
P5.36: JP77.6, U21.31
P5.37: JP77.5, U21.32
P5.38: JP77.8, U21.33
P5.39: JP77.7, U21.34
P5.40: JP94.2, U26.16
P5.41: JP94.1, U26.17
P5.42: JP94.4, U26.18
P5.43: JP94.3, U26.19
P5.44: JP94.6, U26.31
P5.45: JP94.5, U26.32
P5.46: JP94.8, U26.33
P5.47: JP94.7, U26.34
P12.0: JP10.3, U1.53
P12.1: JP10.4, U1.54
P12.2: JP10.5, U1.67
P12.3: JP10.6, U1.68
P12.4: JP34.7, U5.29
P12.5: JP34.8, U5.30
P12.6: JP10.7, U1.29
P12.7: JP10.8, U1.30
P12.8: JP34.5, U5.67
P12.9: JP34.6, U5.68
P12.10: JP34.3, U5.53
P12.11: JP34.4, U5.54
P12.12: JP51.7, U11.29
P12.13: JP51.8, U11.30
P12.14: JP51.5, U11.67
P12.15: JP51.6, U11.68
P12.16: JP51.3, U11.53
P12.17: JP51.4, U11.54
P12.18: JP68.7, U16.29
P12.19: JP68.8, U16.30
P12.20: JP68.5, U16.67
P12.21: JP68.6, U16.68
P12.22: JP68.3, U16.53
P12.23: JP68.4, U16.54
P12.24: JP85.7, U21.29
P12.25: JP85.8, U21.30
P12.26: JP85.5, U21.67
P12.27: JP85.6, U21.68
P12.28: JP85.3, U21.53
P12.29: JP85.4, U21.54
P12.30: JP102.7, U26.29
P12.31: JP102.8, U26.30
P12.32: JP102.5, U26.67
P12.33: JP102.6, U26.68
P12.34: JP102.3, U26.53
P12.35: JP102.4, U26.54
P15.0: C14.1, U1.42, Y2.1
P15.1: C12.1, U1.43, Y2.2
P15.2: C18.1, U1.55, Y1.2
P15.3: C24.1, U1.56, Y1.1
P15.4: C64.1, U5.42, Y4.1
P15.5: C63.1, U5.43, Y4.2
P15.6: C65.1, U5.55, Y3.2
P15.7: C66.1, U5.56, Y3.1
P15.8: C102.1, U11.42, Y6.1
P15.9: C101.1, U11.43, Y6.2
P15.10: C103.1, U11.55, Y5.2
P15.11: C104.1, U11.56, Y5.1
P15.12: C140.1, U16.42, Y8.1
P15.13: C139.1, U16.43, Y8.2
P15.14: C141.1, U16.55, Y7.2
P15.15: C142.1, U16.56, Y7.1
P15.16: C178.1, U21.42, Y10.1
P15.17: C177.1, U21.43, Y10.2
P15.18: C179.1, U21.55, Y9.2
P15.19: C180.1, U21.56, Y9.1
P15.20: C216.1, U26.42, Y12.1
P15.21: C215.1, U26.43, Y12.2
P15.22: C217.1, U26.55, Y11.2
P15.23: C218.1, U26.56, Y11.1
PSOC_D+_BUS: JP1.D+1, R16.2
PSOC_D+_BUS1: JP32.D+1, R11.2
PSOC_D+_BUS2: JP49.D+1, R33.2
PSOC_D+_BUS3: JP66.D+1, R49.2
PSOC_D+_BUS4: JP83.D+1, R65.2
PSOC_D+_BUS5: JP100.D+1, R81.2
PSOC_D+_PAD: R16.1, U1.35
PSOC_D+_PAD1: R11.1, U5.35
PSOC_D+_PAD2: R33.1, U11.35
PSOC_D+_PAD3: R49.1, U16.35
PSOC_D+_PAD4: R65.1, U21.35
PSOC_D+_PAD5: R81.1, U26.35
PSOC_D-_BUS: JP1.D-1, R17.2
PSOC_D-_BUS1: JP32.D-1, R12.2
PSOC_D-_BUS2: JP49.D-1, R34.2
PSOC_D-_BUS3: JP66.D-1, R50.2
PSOC_D-_BUS4: JP83.D-1, R66.2
PSOC_D-_BUS5: JP100.D-1, R82.2
PSOC_D-_PAD: R17.1, U1.36
PSOC_D-_PAD1: R12.1, U5.36
PSOC_D-_PAD2: R34.1, U11.36
PSOC_D-_PAD3: R50.1, U16.36
PSOC_D-_PAD4: R66.1, U21.36
PSOC_D-_PAD5: R82.1, U26.36
VCCA: C1.1, U1.63
VCCA1: C39.1, U5.63
VCCA2: C77.1, U11.63
VCCA3: C115.1, U16.63
VCCA4: C153.1, U21.63
VCCA5: C191.1, U26.63
VCCD: C7.1, U1.39, U1.86
VCCD1: C45.1, U5.39, U5.86
VCCD2: C83.1, U11.39, U11.86
VCCD3: C121.1, U16.39, U16.86
VCCD4: C159.1, U21.39, U21.86
VCCD5: C197.1, U26.39, U26.86
VDDIO: C9.1, C13.1, C15.1, C25.1, C27.1, C29.1, C31.1, JP8.9, JP8.10, JP9.9, JP9.10, JP10.2, JP11.9, JP11.10, JP12.9, JP12.10, JP14.1, JP15.1, JP17.1, R7.2, R8.2, S4.2, U1.26, U1.50, U1.75, U7.17, U7.35, U7.52, U7.67
VDDIO1: C46.1, C48.1, C49.1, C57.1, C58.1, C59.1, C60.1, JP24.9, JP24.10, JP25.9, JP25.10, JP26.9, JP26.10, JP27.9, JP27.10, JP29.1, JP30.1, JP31.1, JP34.2, R29.2, R30.2, S10.2, U5.26, U5.50, U5.75, U6.17, U6.35, U6.52, U6.67
VDDIO2: C84.1, C86.1, C87.1, C95.1, C96.1, C97.1, C98.1, JP41.9, JP41.10, JP42.9, JP42.10, JP43.9, JP43.10, JP44.9, JP44.10, JP46.1, JP47.1, JP48.1, JP51.2, R45.2, R46.2, S16.2, U11.26, U11.50, U11.75, U12.17, U12.35, U12.52, U12.67
VDDIO3: C122.1, C124.1, C125.1, C133.1, C134.1, C135.1, C136.1, JP58.9, JP58.10, JP59.9, JP59.10, JP60.9, JP60.10, JP61.9, JP61.10, JP63.1, JP64.1, JP65.1, JP68.2, R61.2, R62.2, S22.2, U16.26, U16.50, U16.75, U17.17, U17.35, U17.52, U17.67
VDDIO4: C160.1, C162.1, C163.1, C171.1, C172.1, C173.1, C174.1, JP75.9, JP75.10, JP76.9, JP76.10, JP77.9, JP77.10, JP78.9, JP78.10, JP80.1, JP81.1, JP82.1, JP85.2, R77.2, R78.2, S28.2, U21.26, U21.50, U21.75, U22.17, U22.35, U22.52, U22.67
VDDIO5: C198.1, C200.1, C201.1, C209.1, C210.1, C211.1, C212.1, JP92.9, JP92.10, JP93.9, JP93.10, JP94.9, JP94.10, JP95.9, JP95.10, JP97.1, JP98.1, JP99.1, JP102.2, R93.2, R94.2, S34.2, U26.26, U26.50, U26.75, U27.17, U27.35, U27.52, U27.67
VDDIO_ARDUINO: C11.1, JP6.7, JP13.2, S3.2, U1.100
VDDIO_ARDUINO1: C47.1, JP22.7, JP28.2, S9.2, U5.100
VDDIO_ARDUINO2: C85.1, JP39.7, JP45.2, S15.2, U11.100
VDDIO_ARDUINO3: C123.1, JP56.7, JP62.2, S21.2, U16.100
VDDIO_ARDUINO4: C161.1, JP73.7, JP79.2, S27.2, U21.100
VDDIO_ARDUINO5: C199.1, JP90.7, JP96.2, S33.2, U26.100
V_BUS_DEBUG: R4.2, R5.2, U7.18
V_BUS_DEBUG1: R26.2, R27.2, U6.18
V_BUS_DEBUG2: R42.2, R43.2, U12.18
V_BUS_DEBUG3: R58.2, R59.2, U17.18
V_BUS_DEBUG4: R74.2, R75.2, U22.18
V_BUS_DEBUG5: R90.2, R91.2, U27.18
V_BUS_HOST: R3.2, R6.2, U1.27
V_BUS_HOST1: R25.2, R28.2, U5.27
V_BUS_HOST2: R41.2, R44.2, U11.27
V_BUS_HOST3: R57.2, R60.2, U16.27
V_BUS_HOST4: R73.2, R76.2, U21.27
V_BUS_HOST5: R89.2, R92.2, U26.27
V_DEBUG: D2.A, JP2.VBUS1, R4.1
V_DEBUG1: D8.A, JP33.VBUS1, R26.1
V_DEBUG2: D14.A, JP50.VBUS1, R42.1
V_DEBUG3: D20.A, JP67.VBUS1, R58.1
V_DEBUG4: D26.A, JP84.VBUS1, R74.1
V_DEBUG5: D32.A, JP101.VBUS1, R90.1
V_HOST: D1.A, JP1.VBUS1, R3.1
V_HOST1: D7.A, JP32.VBUS1, R25.1
V_HOST2: D13.A, JP49.VBUS1, R41.1
V_HOST3: D19.A, JP66.VBUS1, R57.1
V_HOST4: D25.A, JP83.VBUS1, R73.1
V_HOST5: D31.A, JP100.VBUS1, R89.1
V_IN: D4.C, JP6.1, SJ1.2, SJ2.2, U2.1, U2.3, U3.1, U3.3
V_IN1: D10.C, JP22.1, SJ8.2, SJ9.2, U8.1, U8.3, U9.1, U9.3
V_IN2: D16.C, JP39.1, SJ15.2, SJ16.2, U13.1, U13.3, U14.1, U14.3
V_IN3: D22.C, JP56.1, SJ22.2, SJ23.2, U18.1, U18.3, U19.1, U19.3
V_IN4: D28.C, JP73.1, SJ29.2, SJ30.2, U23.1, U23.3, U24.1, U24.3
V_IN5: D34.C, JP90.1, SJ36.2, SJ37.2, U28.1, U28.3, U29.1, U29.3
